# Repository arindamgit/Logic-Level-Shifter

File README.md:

# Logic-Level-Shifter
The circuit can be used to convert voltages ranging from +/-6V to 0/3.3/5.0V. The potentiometer can be used to adjust required output swing

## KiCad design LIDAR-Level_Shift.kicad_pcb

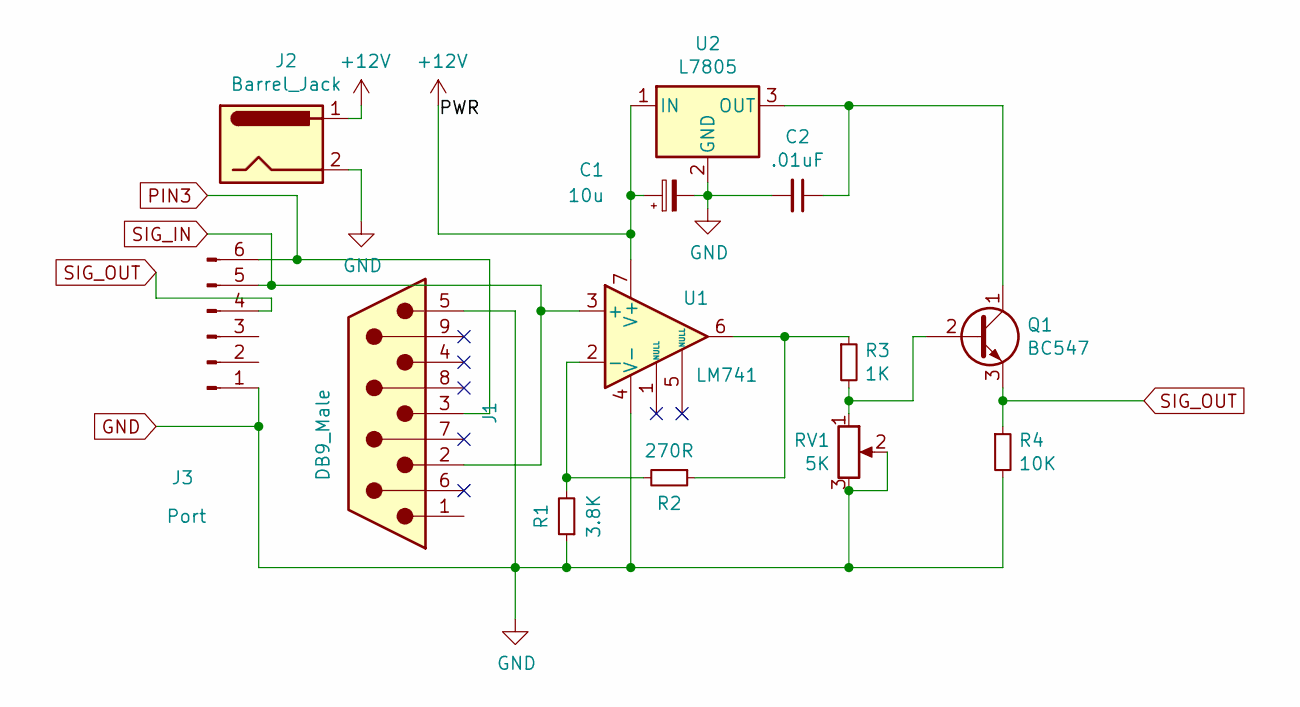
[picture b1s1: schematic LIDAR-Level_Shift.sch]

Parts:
C1: 10u; C_Radial_D4.0mm_H5.0mm_P1.50mm
C2: .01uF; C_Disc_D3.0mm_W2.0mm_P2.50mm
J1: DB9_Male; DSUB-9_Male_Horizontal_P2.77x2.84mm_EdgePinOffset9.40mm
J2: Barrel_Jack; BarrelJack_CUI_PJ-102AH_Horizontal
J3: Port; PinHeader_1x06_P2.00mm_Vertical
Q1: BC547; TO-92_Inline
R1: 3.8K; R_Axial_DIN0204_L3.6mm_D1.6mm_P7.62mm_Horizontal
R2: 270R; R_Axial_DIN0204_L3.6mm_D1.6mm_P7.62mm_Horizontal
R3: 1K; R_Axial_DIN0204_L3.6mm_D1.6mm_P7.62mm_Horizontal
R4: 10K; R_Axial_DIN0204_L3.6mm_D1.6mm_P7.62mm_Horizontal
RV1: 5K; Potentiometer_Bourns_3266Y_Vertical
U1: LM741; DIP-8_W7.62mm_LongPads
U2: L7805; TO-220-3_Vertical

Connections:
+12V: C1.1, J2.1, U1.7 (V+), U2.1 (IN)
GND: C1.2, C2.2, J1.5, J2.2, J3.1, R1.1, R4.2, RV1.2, RV1.3, U1.4 (V-), U2.2 (GND)
unnamed: C2.1, Q1.1 (C), U2.3 (OUT)
unnamed: Q1.2 (B), R3.2, RV1.1
unnamed: R1.2, R2.2, U1.2 (-)
unnamed: R2.1, R3.1, U1.6
PIN3: J1.3, J3.6
SIG_IN: J1.2, J3.5, U1.3 (+)
SIG_OUT: J3.4, Q1.3 (E), R4.1

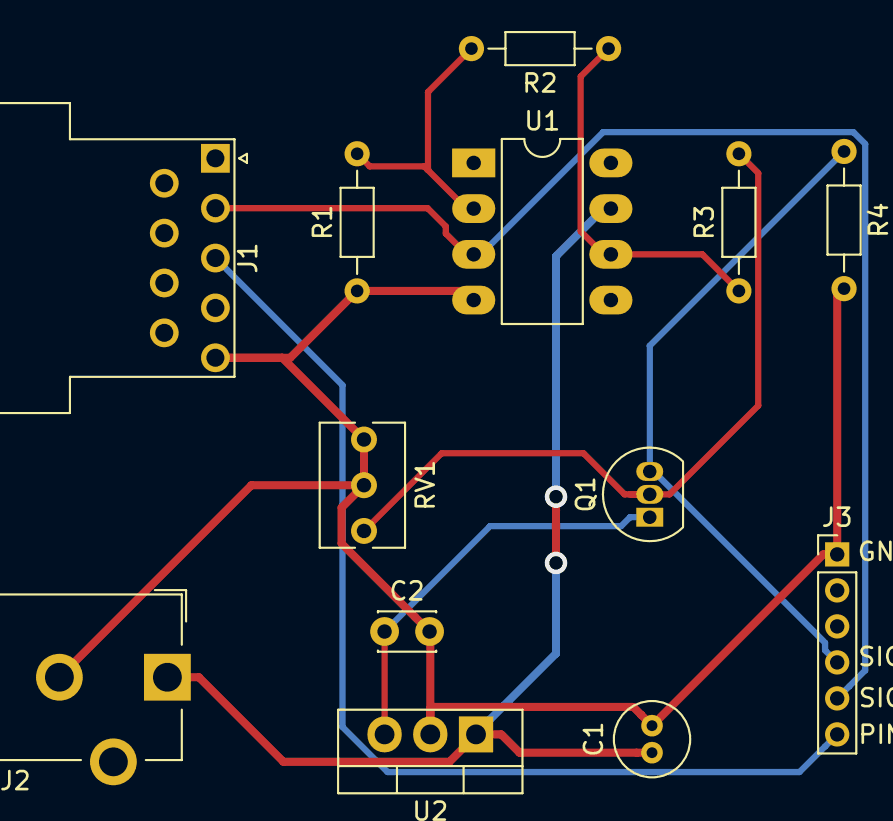
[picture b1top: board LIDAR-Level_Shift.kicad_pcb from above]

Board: 2 copper layers, 13 parts (0 on the bottom side), 9 nets.

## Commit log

2019-10-24 First Push
